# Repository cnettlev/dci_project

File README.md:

# dci_project

Este proyecto es para el curso de **Diseño de Circuitos Impresos**.

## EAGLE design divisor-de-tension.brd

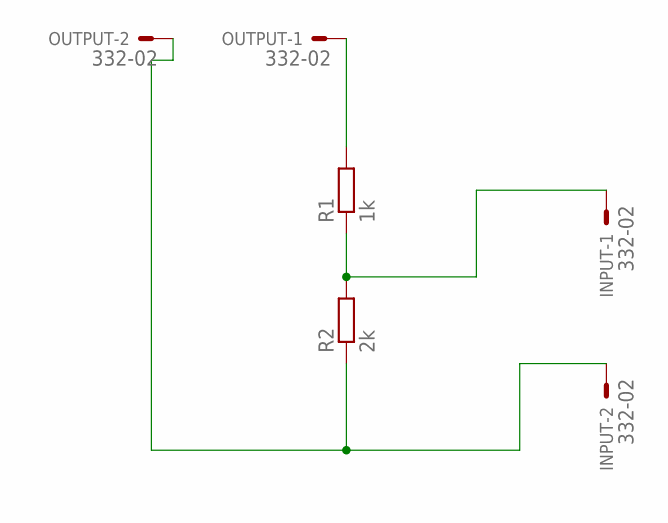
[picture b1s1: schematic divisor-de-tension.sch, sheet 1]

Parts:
INPUT: 332-02
OUTPUT: 332-02
R1: 1k; 0207/10
R2: 2k; 0207/10

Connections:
unnamed: OUTPUT.1, R1.2
unnamed: INPUT.2, OUTPUT.2, R2.1
unnamed: INPUT.1, R1.1, R2.2

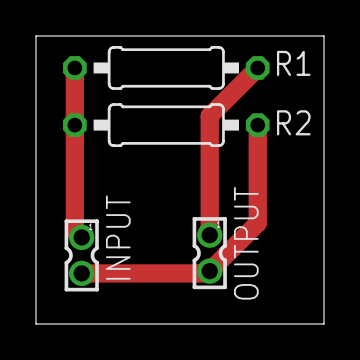
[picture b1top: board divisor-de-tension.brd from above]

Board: 2 copper layers, 16.0 x 16.0 mm, 4 parts (0 on the bottom side), 3 nets.

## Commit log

2021-09-02 Añade conector de poder
